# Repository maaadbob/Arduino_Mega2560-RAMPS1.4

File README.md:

Arduino_Mega2560-RAMPS1.4
=========================

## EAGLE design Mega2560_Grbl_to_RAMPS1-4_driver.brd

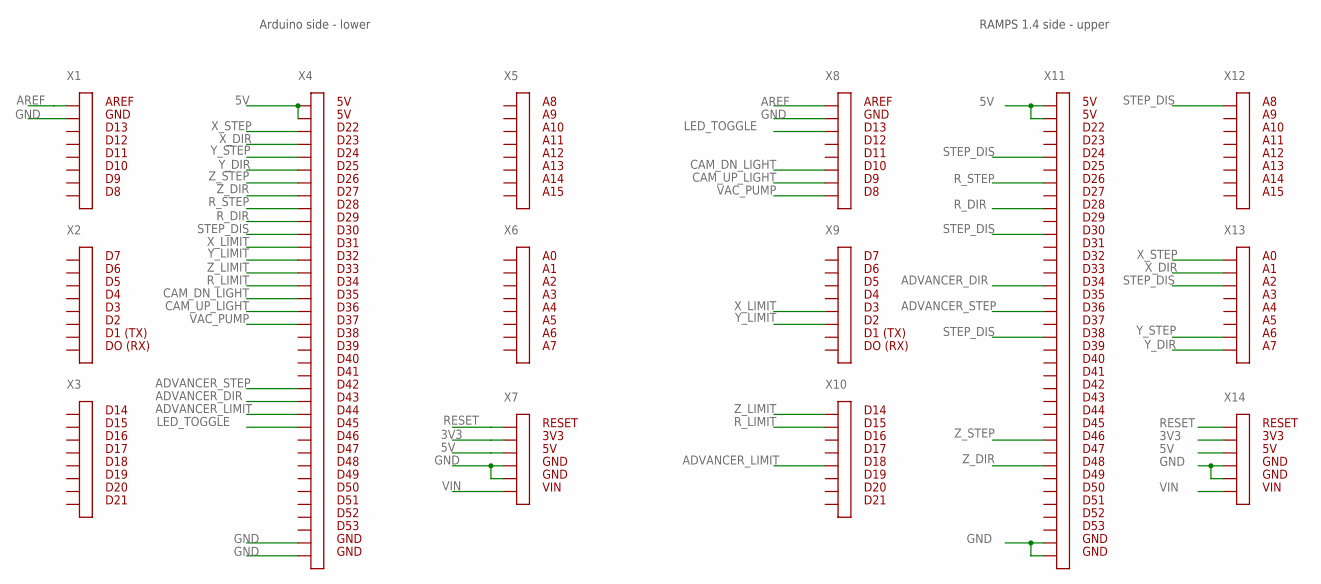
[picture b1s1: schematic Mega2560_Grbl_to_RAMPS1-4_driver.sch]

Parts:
X1, X2, X3, X5, X6: M20-9770842; 8X1-P2.54-D1.00
X4: M20-9761842FLIP; 18X2-P2.54-D1.00
X7: M20-9770642; 6X1-P2.54-D1.00
X8, X9, X10, X12, X13: M20-7820842; 8X1-P2.54-D1.00
X11: M20-7831842; 18X2-P2.54-D1.00
X14: M20-7820642; 6X1-P2.54-D1.00

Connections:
3V3: X7.P$2, X14.P$2
5V: X4.P$1, X4.P$2, X7.P$3, X11.P$1, X11.P$2, X14.P$3
ADVANCER_DIR: X4.P$23, X11.P$15
ADVANCER_LIMIT: X4.P$26, X10.P$5
ADVANCER_STEP: X4.P$24, X11.P$17
AREF: X1.P$1, X8.P$1
CAM_DN_LIGHT: X4.P$15, X8.P$6
CAM_UP_LIGHT: X4.P$18, X8.P$7
GND: X1.P$2, X4.P$35, X4.P$36, X7.P$4, X7.P$5, X8.P$2, X11.P$35, X11.P$36, X14.P$4, X14.P$5
LED_TOGGLE: X4.P$25, X8.P$3
RESET: X7.P$1, X14.P$1
R_DIR: X4.P$9, X11.P$9
R_LIMIT: X4.P$16, X10.P$2
R_STEP: X4.P$10, X11.P$7
STEP_DIS: X4.P$12, X11.P$5, X11.P$11, X11.P$19, X12.P$1, X13.P$3
VAC_PUMP: X4.P$17, X8.P$8
VIN: X7.P$6, X14.P$6
X_DIR: X4.P$3, X13.P$2
X_LIMIT: X4.P$11, X9.P$5
X_STEP: X4.P$4, X13.P$1
Y_DIR: X4.P$5, X13.P$8
Y_LIMIT: X4.P$14, X9.P$6
Y_STEP: X4.P$6, X13.P$7
Z_DIR: X4.P$7, X11.P$29
Z_LIMIT: X4.P$13, X10.P$1
Z_STEP: X4.P$8, X11.P$27

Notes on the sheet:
Arduino side - lower
RAMPS 1.4 side - upper
AREF
GND
D13
D12
D11
D10
D1 (TX)
DO (RX)
D14
D15
D16
D17
D18
D19
D20
D21
D22
D23
D24
D25
D26
D27
D28
D29
D30
D31
D32
D33
D34
D35
D36
D37
D38
D39
D40
D41
D42
D43

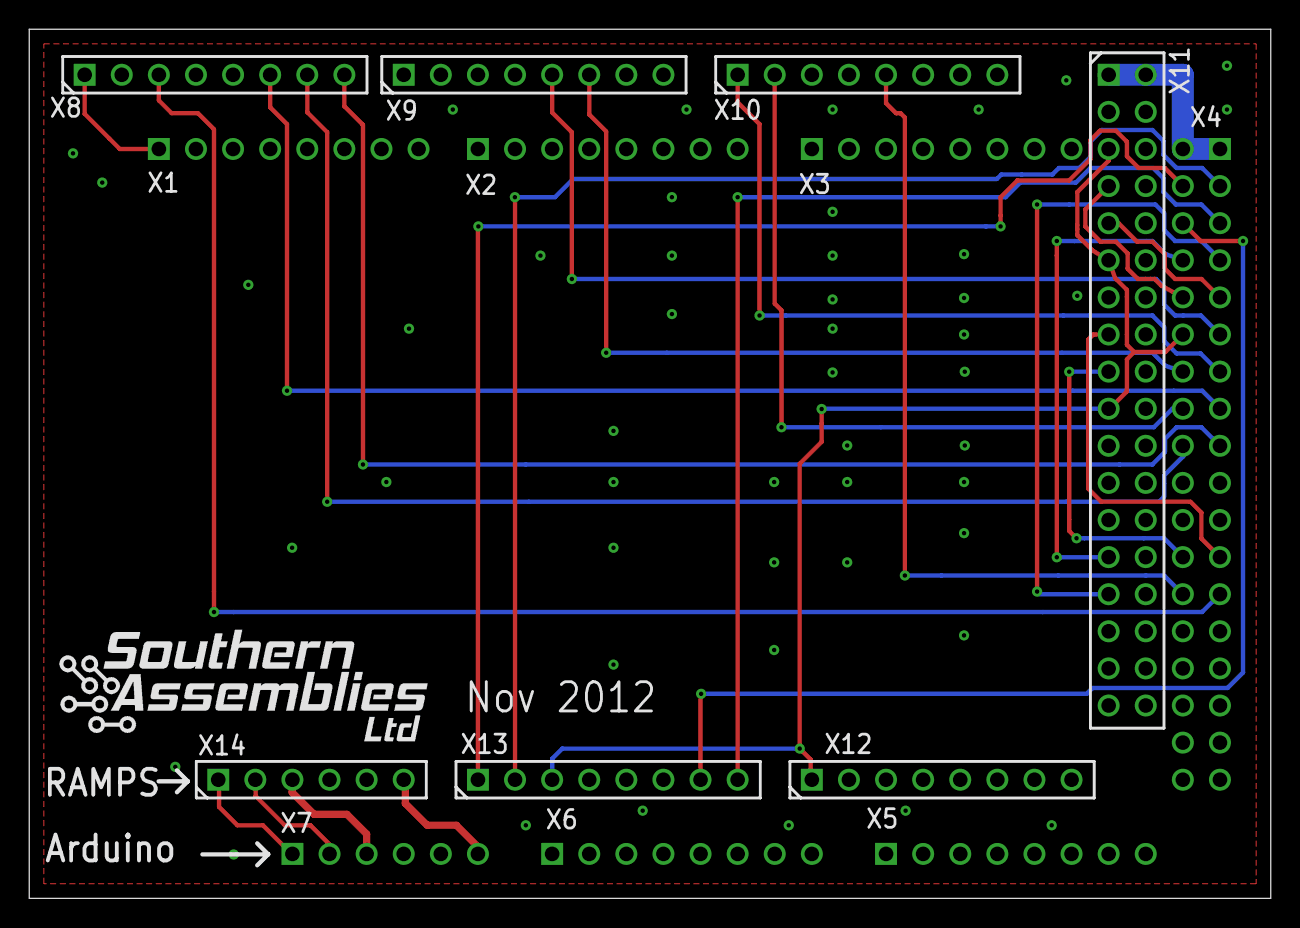
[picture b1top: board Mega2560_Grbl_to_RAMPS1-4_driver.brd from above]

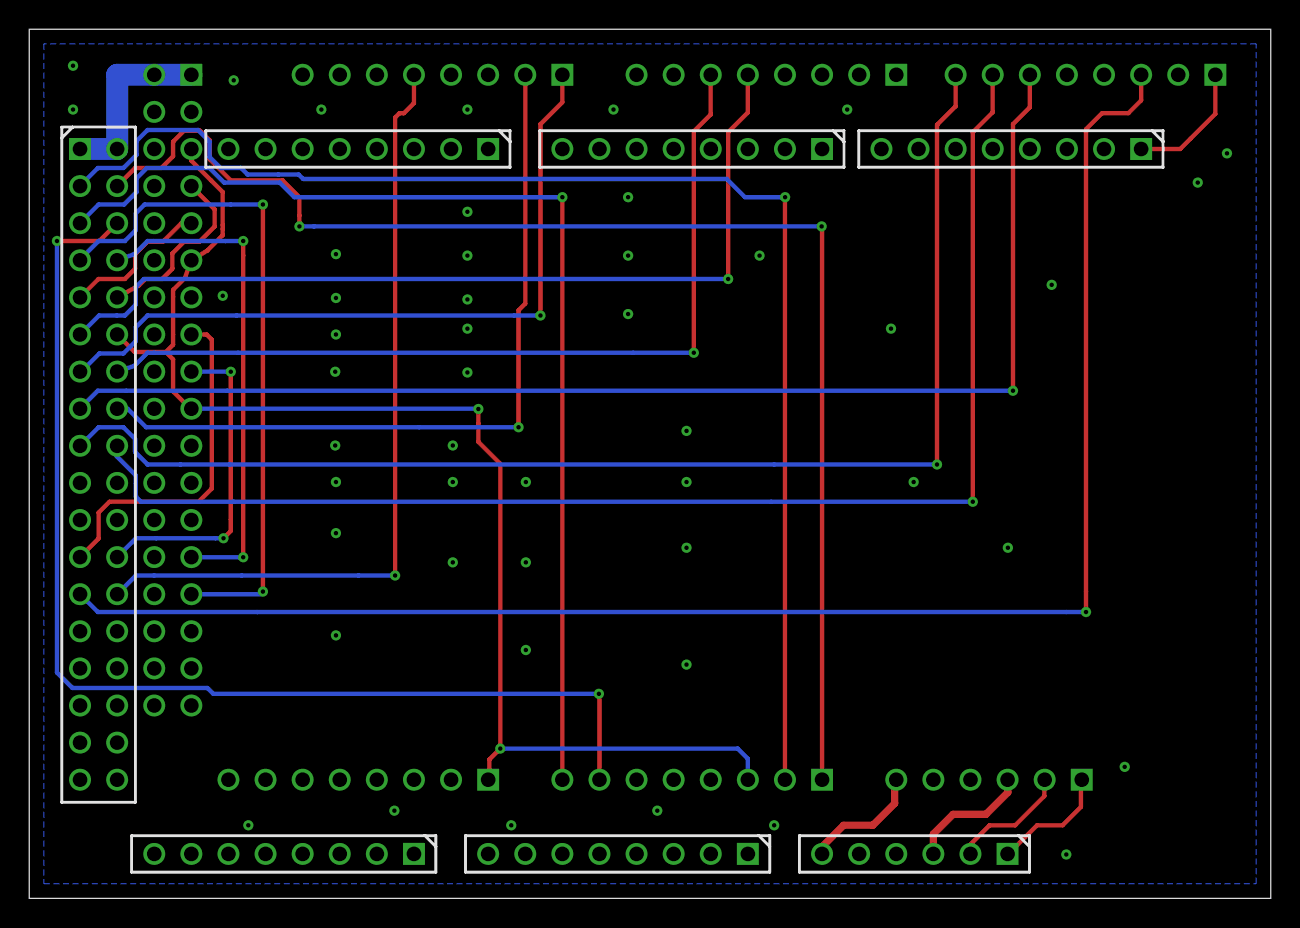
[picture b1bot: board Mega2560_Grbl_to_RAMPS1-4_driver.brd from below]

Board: 2 copper layers, 85.0 x 59.5 mm, 14 parts (7 on the bottom side), 26 nets.

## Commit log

2014-09-06 Arduino Mega2560 to RAMPS1.4 stepper board PCB
    Signal routing PCB connecting an Arduino Mega2560 to a RAMPS1.4 stepper
    controller board.
    Allows GRBL users access to an off-the-shelf stepper driver solution.
